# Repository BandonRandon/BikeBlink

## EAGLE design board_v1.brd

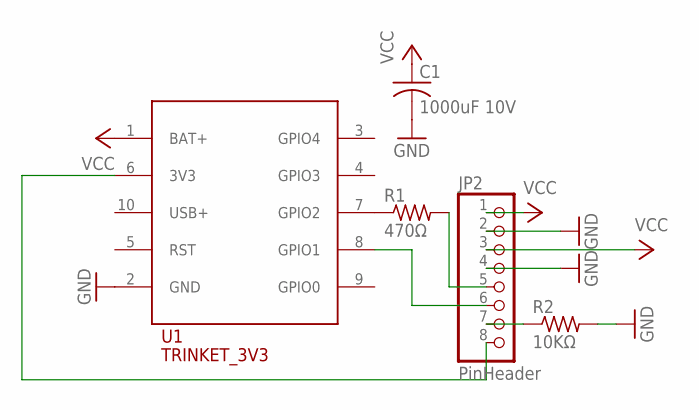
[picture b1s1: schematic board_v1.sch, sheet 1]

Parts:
C1: 1000uF 10V; C050-025X075
JP2: PinHeader; 1X08-LOCK
R1: 470Ω; 0204/7
R2: 10KΩ; 0204/7
U1: TRINKET_3V3

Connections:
GND: C1.2, JP2.2, JP2.4, R2.2, U1.2 (GND)
unnamed: R1.1, U1.7 (GPIO2)
unnamed: JP2.5, R1.2
unnamed: JP2.8, U1.6 (3V3)
unnamed: JP2.6, U1.8 (GPIO1)
unnamed: JP2.7, R2.1
VCC: C1.1, JP2.1, JP2.3, U1.1 (BAT+)

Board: 2 copper layers, 5 parts (0 on the bottom side), 7 nets, no tracks yet.

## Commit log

2016-03-12 Inital commit
